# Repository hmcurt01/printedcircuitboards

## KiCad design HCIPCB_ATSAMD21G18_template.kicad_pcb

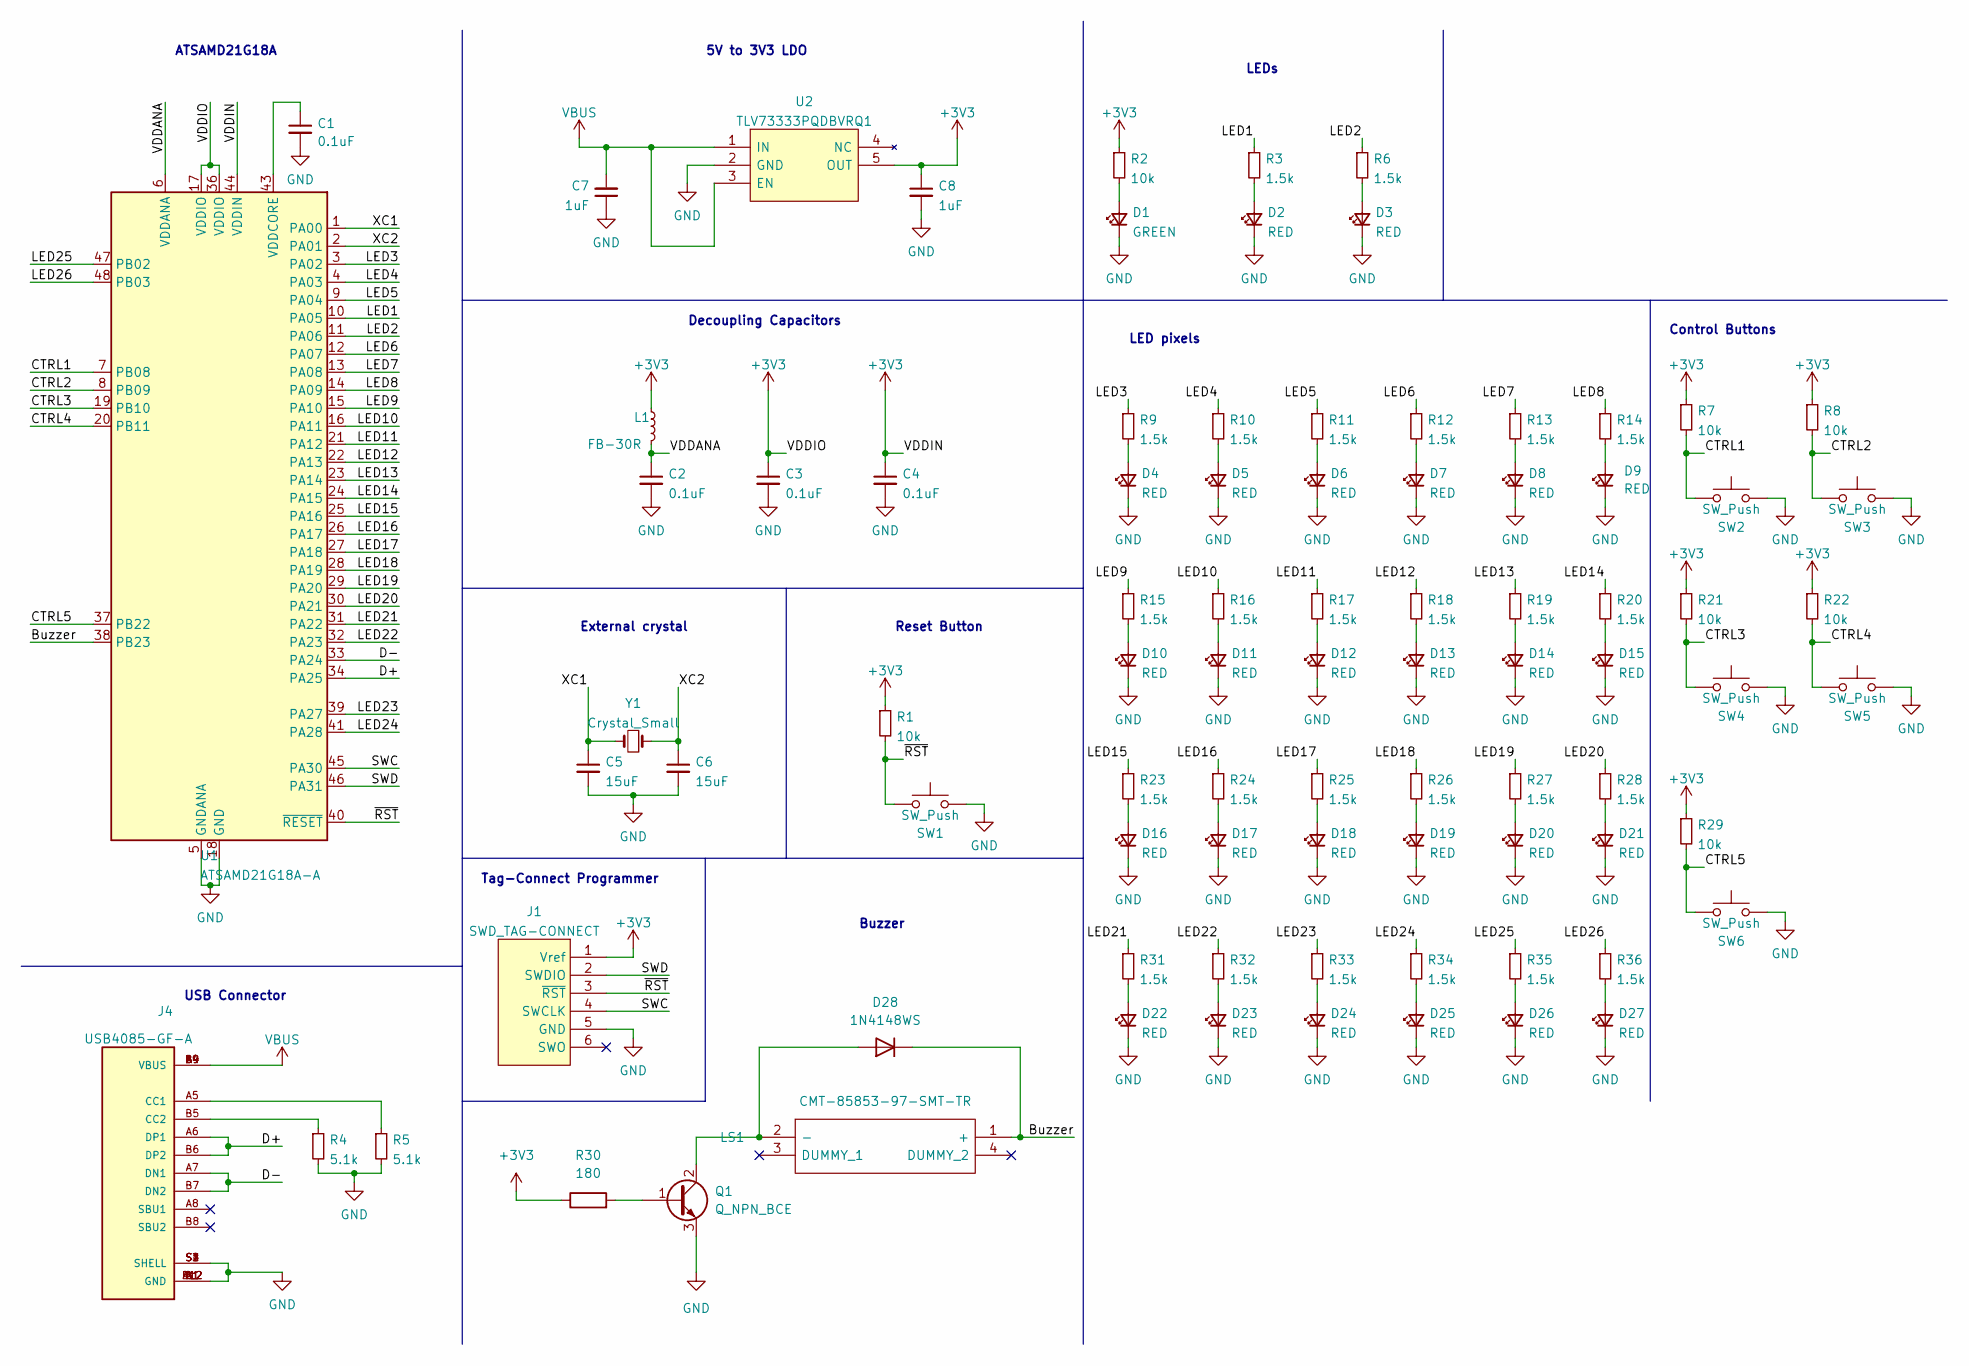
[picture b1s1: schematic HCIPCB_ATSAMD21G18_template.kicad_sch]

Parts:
C1, C2, C3, C4: 0.1uF; C_0603_1608Metric
C5, C6: 15uF; C_0603_1608Metric
C7, C8: 1uF; C_0603_1608Metric
D1: GREEN; LED_0603_1608Metric
D2, D3, D4, D5, D6, D7, D8, D9, D10, D11, D12, D13, D14, D15, D16, D17, D18, D19, D20, D21, D22, D23, D24, D25, D26, D27: RED; LED_0603_1608Metric
D28: 1N4148WS; D_0603_1608Metric_Pad1.05x0.95mm_HandSolder
J1: SWD_TAG-CONNECT; Tag-Connect_TC2030-IDC-FP_2x03_P1.27mm_Vertical
J4: USB4085-GF-A; GCT_USB4085-GF-A; PARTREV A4
L1: FB-30R; L_0603_1608Metric
LS1: CMT-85853-97-SMT-TR; CMT8585397SMTTR; Mouser Part Number 490-CMT8585397SMTTR
Q1: Q_NPN_BCE; SOT-23-3
R1, R2, R7, R8, R21, R22, R29: 10k; R_0603_1608Metric
R3, R6, R9, R10, R11, R12, R13, R14, R15, R16, R17, R18, R19, R20, R23, R24, R25, R26, R27, R28, R31, R32, R33, R34, R35, R36: 1.5k; R_0603_1608Metric
R4, R5: 5.1k; R_0603_1608Metric
R30: 180; R_0603_1608Metric_Pad0.98x0.95mm_HandSolder
SW1, SW2, SW3, SW4, SW5, SW6: SW_Push; SW_SPST_TL3305A
U1: ATSAMD21G18A-A; TQFP-48_7x7mm_P0.5mm
U2: TLV73333PQDBVRQ1; SOT95P280X145-5N; Mouser Part Number 595-TLV73333PQDBVRQ1
Y1: Crystal_Small; Crystal_SMD_3215-2Pin_3.2x1.5mm

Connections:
+3V3: C3.1, C4.1, C8.1, J1.1 (Vref), L1.1, R1.1, R2.1, R7.1, R8.1, R21.1, R22.1, R29.1, R30.1, U1.17 (VDDIO), U1.36 (VDDIO), U1.44 (VDDIN), U2.5 (OUT)
/Buzzer: D28.1 (K), LS1.1 (+), U1.38 (PB23)
/CTRL1: R7.2, SW2.1, U1.7 (PB08)
/CTRL2: R8.2, SW3.1, U1.8 (PB09)
/CTRL3: R21.2, SW4.1, U1.19 (PB10)
/CTRL4: R22.2, SW5.1, U1.20 (PB11)
/CTRL5: R29.2, SW6.1, U1.37 (PB22)
/D+: J4.A6 (DP1), J4.B6 (DP2), U1.34 (PA25)
/D-: J4.A7 (DN1), J4.B7 (DN2), U1.33 (PA24)
/LED1: R3.1, U1.10 (PA05)
/LED2: R6.1, U1.11 (PA06)
/LED3: R9.1, U1.3 (PA02)
/LED4: R10.1, U1.4 (PA03)
/LED5: R11.1, U1.9 (PA04)
/LED6: R12.1, U1.12 (PA07)
/LED7: R13.1, U1.13 (PA08)
/LED8: R14.1, U1.14 (PA09)
/LED9: R15.1, U1.15 (PA10)
/LED10: R16.1, U1.16 (PA11)
/LED11: R17.1, U1.21 (PA12)
/LED12: R18.1, U1.22 (PA13)
/LED13: R19.1, U1.23 (PA14)
/LED14: R20.1, U1.24 (PA15)
/LED15: R23.1, U1.25 (PA16)
/LED16: R24.1, U1.26 (PA17)
/LED17: R25.1, U1.27 (PA18)
/LED18: R26.1, U1.28 (PA19)
/LED19: R27.1, U1.29 (PA20)
/LED20: R28.1, U1.30 (PA21)
/LED21: R31.1, U1.31 (PA22)
/LED22: R32.1, U1.32 (PA23)
/LED23: R33.1, U1.39 (PA27)
/LED24: R34.1, U1.41 (PA28)
/LED25: R35.1, U1.47 (PB02)
/LED26: R36.1, U1.48 (PB03)
/SWC: J1.4 (SWCLK), U1.45 (PA30)
/SWD: J1.2 (SWDIO), U1.46 (PA31)
/VDDANA: C2.1, L1.2, U1.6 (VDDANA)
/XC1: C5.1, U1.1 (PA00), Y1.2
/XC2: C6.1, U1.2 (PA01), Y1.1
/~RST: J1.3 (~RST), R1.2, SW1.1, U1.40 (~RESET)
GND: C1.2, C2.2, C3.2, C4.2, C5.2, C6.2, C7.1, C8.2, D1.1 (K), D2.1 (K), D3.1 (K), D4.1 (K), D5.1 (K), D6.1 (K), D7.1 (K), D8.1 (K), D9.1 (K), D10.1 (K), D11.1 (K), D12.1 (K), D13.1 (K), D14.1 (K), D15.1 (K), D16.1 (K), D17.1 (K), D18.1 (K), D19.1 (K), D20.1 (K), D21.1 (K), D22.1 (K), D23.1 (K), D24.1 (K), D25.1 (K), D26.1 (K), D27.1 (K), J1.5 (GND), J4.A1 (GND), J4.A12 (GND), J4.B1 (GND), J4.B12 (GND), J4.S1 (SHELL), J4.S2 (SHELL), J4.S3 (SHELL), J4.S4 (SHELL), Q1.3 (E), R4.2, R5.2, SW1.2, SW2.2, SW3.2, SW4.2, SW5.2, SW6.2, U1.5 (GNDANA), U1.18 (GND), U1.35 (GND), U1.42 (GND), U2.2 (GND)
unnamed: C1.1, U1.43 (VDDCORE)
unnamed: D1.2 (A), R2.2
unnamed: D2.2 (A), R3.2
unnamed: D3.2 (A), R6.2
unnamed: D4.2 (A), R9.2
unnamed: D5.2 (A), R10.2
unnamed: D6.2 (A), R11.2
unnamed: D7.2 (A), R12.2
unnamed: D8.2 (A), R13.2
unnamed: D9.2 (A), R14.2
unnamed: D10.2 (A), R15.2
unnamed: D11.2 (A), R16.2
unnamed: D12.2 (A), R17.2
unnamed: D13.2 (A), R18.2
unnamed: D14.2 (A), R19.2
unnamed: D15.2 (A), R20.2
unnamed: D16.2 (A), R23.2
unnamed: D17.2 (A), R24.2
unnamed: D18.2 (A), R25.2
unnamed: D19.2 (A), R26.2
unnamed: D20.2 (A), R27.2
unnamed: D21.2 (A), R28.2
unnamed: D22.2 (A), R31.2
unnamed: D23.2 (A), R32.2
unnamed: D24.2 (A), R33.2
unnamed: D25.2 (A), R34.2
unnamed: D26.2 (A), R35.2
unnamed: D27.2 (A), R36.2
unnamed: D28.2 (A), LS1.2 (-), Q1.2 (C)
unnamed: J4.A5 (CC1), R5.1
unnamed: J4.B5 (CC2), R4.1
unnamed: Q1.1 (B), R30.2
VBUS: C7.2, J4.A4 (VBUS), J4.A9 (VBUS), J4.B4 (VBUS), J4.B9 (VBUS), U2.1 (IN), U2.3 (EN)

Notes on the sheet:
5V to 3V3 LDO
Control Buttons
External crystal
Tag-Connect Programmer
Decoupling Capacitors
Buzzer
LEDs
USB Connector
ATSAMD21G18A
Reset Button
LED pixels

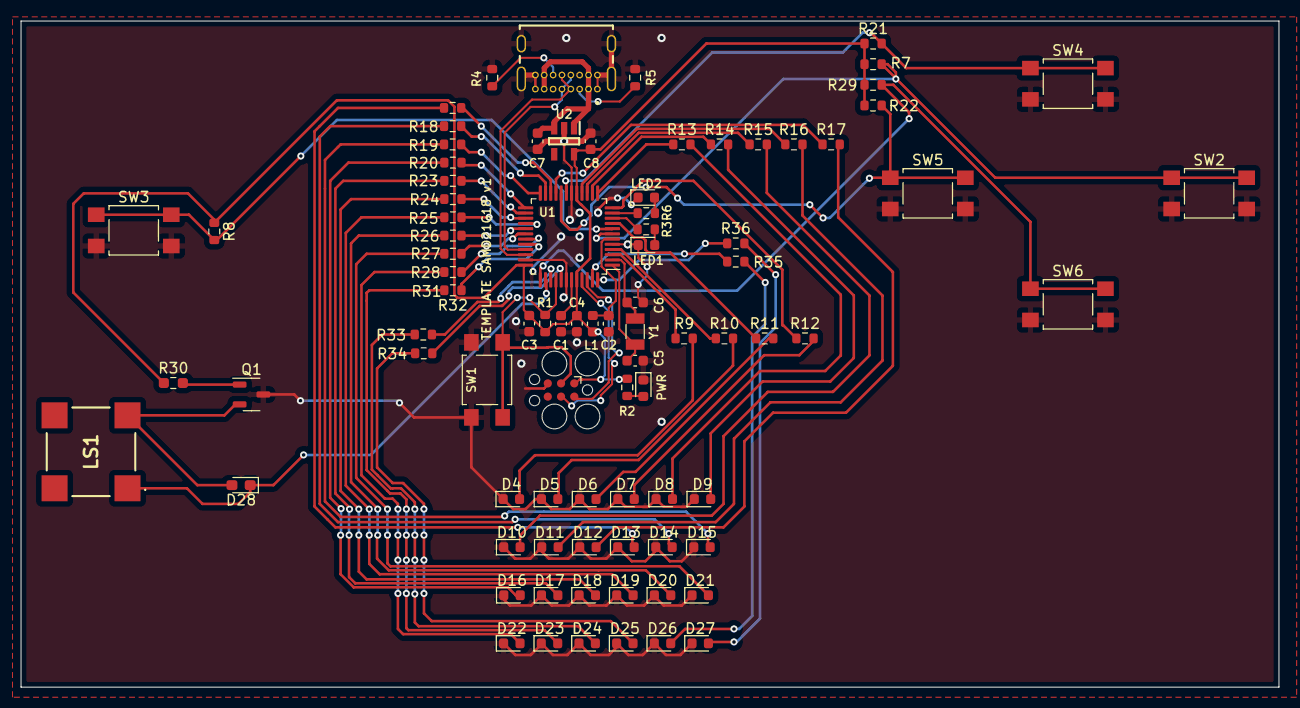
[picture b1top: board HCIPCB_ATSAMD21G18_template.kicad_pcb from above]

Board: 2 copper layers, 120.7 x 63.9 mm, 86 parts (0 on the bottom side), 75 nets.

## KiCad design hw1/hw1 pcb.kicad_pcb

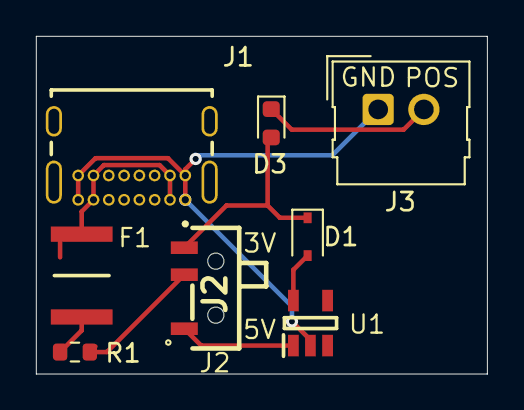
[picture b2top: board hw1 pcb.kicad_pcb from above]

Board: 2 copper layers, 25.1 x 18.8 mm, 8 parts (0 on the bottom side), 9 nets.

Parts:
D1: 1N4148WS; D_SOD-323
D3: LED; LED_0603_1608Metric
F1: MF-MSMF050-2; FUSC4632X85N
J1: USB4085-GF-A; GCT_USB4085-GF-A
J2: SSSS810701
J3: Conn_01x02_Male; Molex_SL_171971-0002_1x02_P2.54mm_Vertical
R1: R; R_0603_1608Metric
U1: TLV73333PQDBVRQ1; SOT95P280X145-5N

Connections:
GND: J1.A1 (GND), J1.A12 (GND), J1.B1 (GND), J1.B12 (GND), J3.1, U1.2 (GND)
unnamed: D1.2 (A), U1.5 (OUT)
unnamed: D3.1 (K), J3.2
unnamed: F1.1, J1.A4 (VBUS), J1.A9 (VBUS), J1.B4 (VBUS), J1.B9 (VBUS)
unnamed: F1.2, R1.1
unnamed: J1.S1 (SHELL), J1.S2 (SHELL), J1.S3 (SHELL), J1.S4 (SHELL)
unnamed: J2.1, U1.1 (IN)
unnamed: J2.2, R1.2
unnamed: D1.1 (K), D3.2 (A), J2.3

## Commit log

2023-01-10 Finished
